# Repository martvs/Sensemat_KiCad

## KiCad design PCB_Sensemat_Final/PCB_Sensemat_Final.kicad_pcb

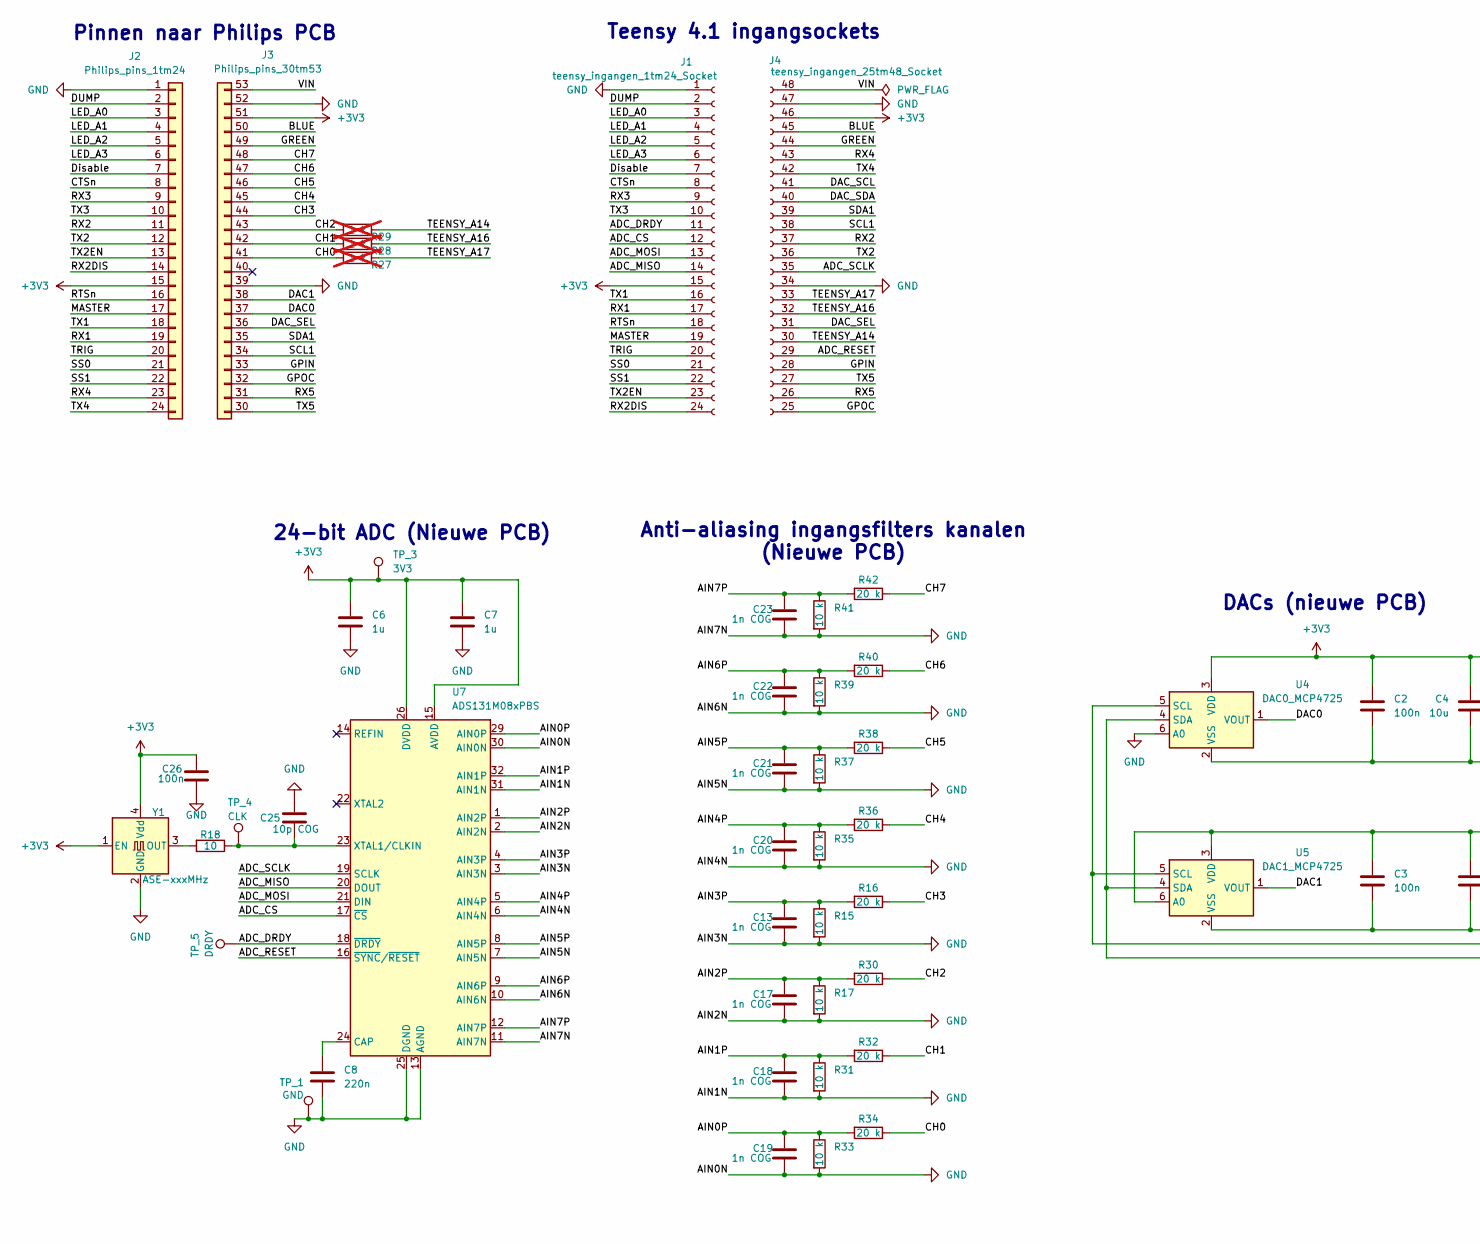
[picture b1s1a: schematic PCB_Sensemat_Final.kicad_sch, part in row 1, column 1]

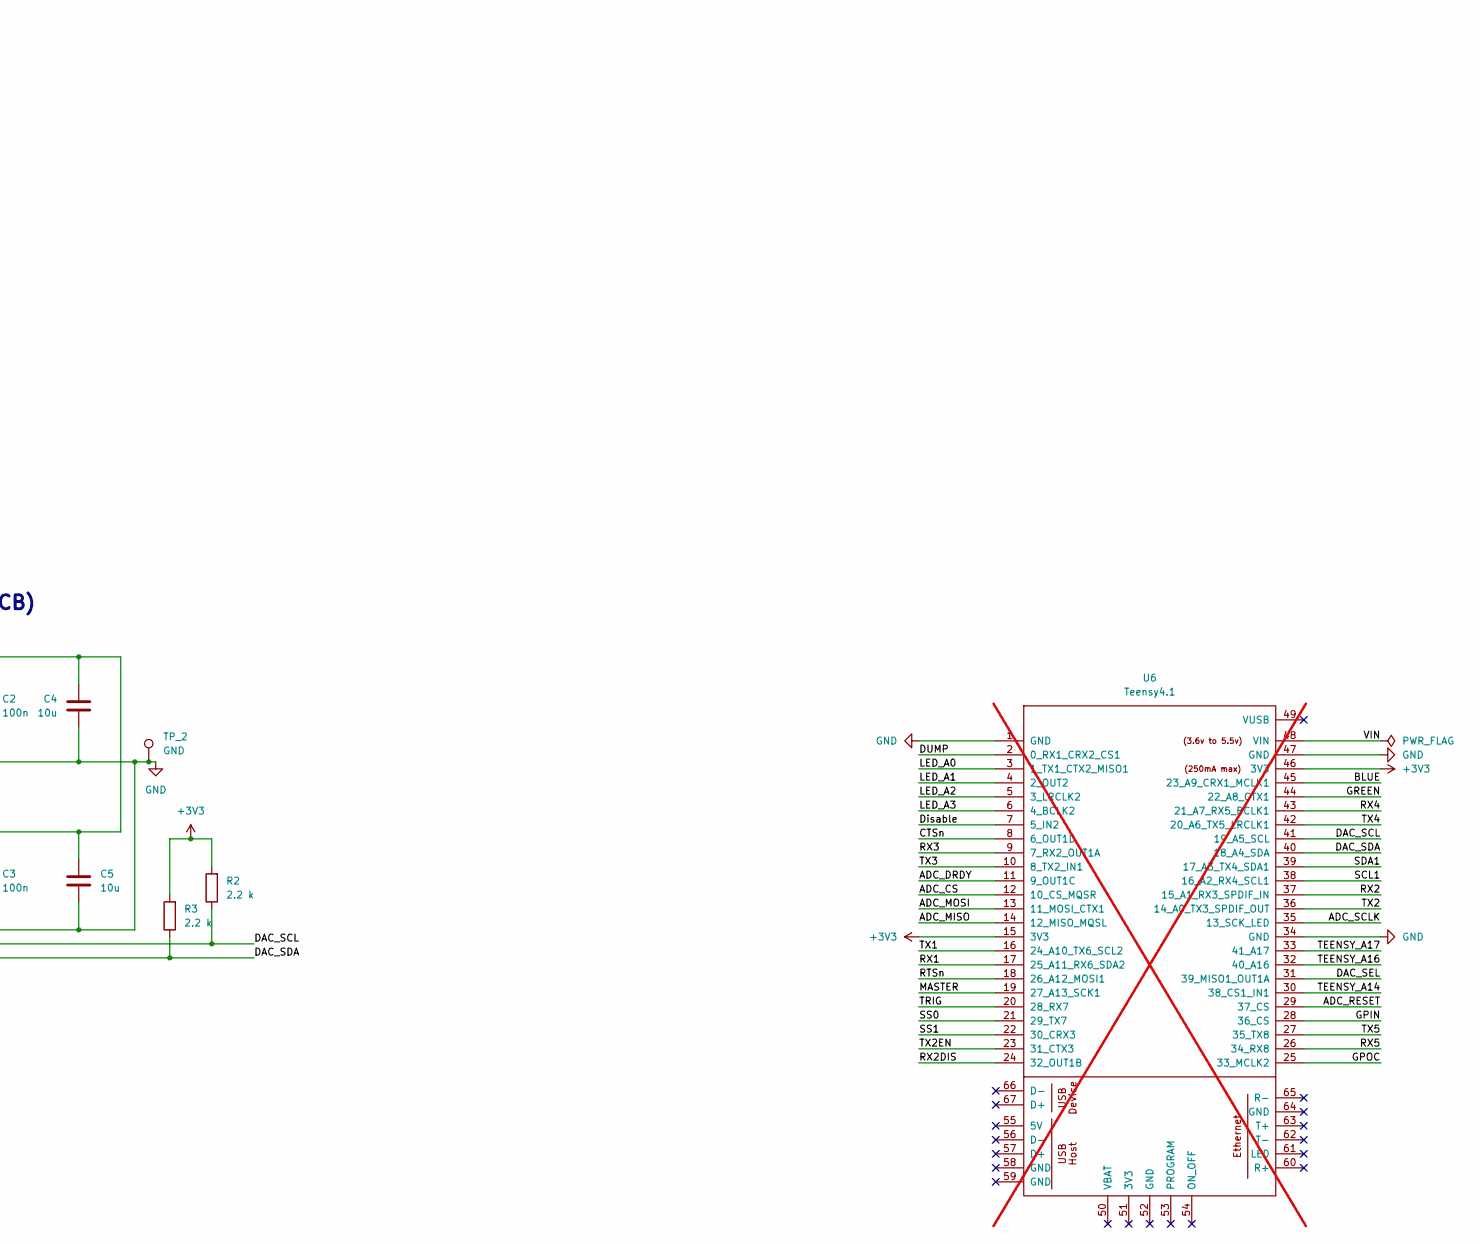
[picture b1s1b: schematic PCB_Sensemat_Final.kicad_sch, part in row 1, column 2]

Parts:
C2, C3, C26: 100n; C_0805_2012Metric_Pad1.18x1.45mm_HandSolder; LCSC C49678
C4, C5: 10u; C_0805_2012Metric_Pad1.18x1.45mm_HandSolder; LCSC C15850
C6, C7: 1u; C_0805_2012Metric_Pad1.18x1.45mm_HandSolder; LCSC C28323
C8: 220n; C_0805_2012Metric_Pad1.18x1.45mm_HandSolder; LCSC C5378
C13, C17, C18, C19, C20, C21, C22, C23: 1n COG; C_0805_2012Metric_Pad1.18x1.45mm_HandSolder; LCSC C29925
C25: 10p COG; C_0805_2012Metric_Pad1.18x1.45mm_HandSolder; LCSC C107107
J1: teensy_ingangen_1tm24_Socket; PinSocket_1x24_P2.54mm_Vertical
J2: Philips_pins_1tm24; PinHeader_1x24_P2.54mm_Vertical
J3: Philips_pins_30tm53; PinHeader_1x24_nieuw_final_P2.54mm_Vertical
J4: teensy_ingangen_25tm48_Socket; PinSocket_ingang_teensy_1x24_P2.54mm_Vertical
R2, R3: 2.2 k; R_0805_2012Metric_Pad1.20x1.40mm_HandSolder; LCSC C17520
R15, R17, R31, R33, R35, R37, R39, R41: 10 k; R_0805_2012Metric_Pad1.20x1.40mm_HandSolder; LCSC C346681
R16, R30, R32, R34, R36, R38, R40, R42: 20 k; R_0805_2012Metric_Pad1.20x1.40mm_HandSolder; LCSC C844680
R18: 10; R_0805_2012Metric_Pad1.20x1.40mm_HandSolder; LCSC C17415
R27, R28, R29: 1 k; R_0805_2012Metric_Pad1.20x1.40mm_HandSolder; not fitted
TP_1, TP_2: GND; TestPoint_THTPad_D2.0mm_Drill1.0mm
TP_3: 3V3; TestPoint_Pad_D1.5mm
TP_4: CLK; TestPoint_Pad_D1.5mm
TP_5: DRDY; TestPoint_Pad_D1.5mm
U4: DAC0_MCP4725; SOT-23-6; LCSC C144198
U5: DAC1_MCP4725; SOT-23-6; LCSC C144198
U6: Teensy4.1; Teensy41; not fitted
U7: ADS131M08xPBS; TQFP-32_5x5mm_P0.5mm; LCSC C2862610
Y1: ASE-xxxMHz; Oscillator_SMD_Abracon_ASE-4Pin_3.2x2.5mm; LCSC C252332

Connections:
+3V3: C2.1, C3.1, C4.1, C5.1, C6.1, C7.1, C26.1, J1.15, J2.15, J3.51 (Pin_3), J4.46 (Pin_3), R2.2, R3.2, TP_3.1 (1_1), U4.3 (VDD), U5.3 (VDD), U5.6 (A0), U6.15 (3V3), U6.46 (3V3), U7.15 (AVDD), U7.26 (DVDD), Y1.1 (EN), Y1.4 (Vdd)
/ADC_CS: J1.12, U6.12 (10_CS_MQSR), U7.17 (~CS)
/ADC_DRDY: J1.11, TP_5.1 (1_1), U6.11 (9_OUT1C), U7.18 (~DRDY)
/ADC_MISO: J1.14, U6.14 (12_MISO_MQSL), U7.20 (DOUT)
/ADC_MOSI: J1.13, U6.13 (11_MOSI_CTX1), U7.21 (DIN)
/ADC_RESET: J4.29 (Pin_20), U6.29 (37_CS), U7.16 (~SYNC/~RESET)
/ADC_SCLK: J4.35 (Pin_14), U6.35 (13_SCK_LED), U7.19 (SCLK)
/AIN0P: C19.1, R33.1, R34.2, U7.29 (AIN0P)
/AIN1P: C18.1, R31.1, R32.2, U7.32 (AIN1P)
/AIN2P: C17.1, R17.1, R30.2, U7.1 (AIN2P)
/AIN3P: C13.1, R15.1, R16.2, U7.4 (AIN3P)
/AIN4P: C20.1, R35.1, R36.2, U7.5 (AIN4P)
/AIN5P: C21.1, R37.1, R38.2, U7.8 (AIN5P)
/AIN6P: C22.1, R39.1, R40.2, U7.9 (AIN6P)
/AIN7P: C23.1, R41.1, R42.2, U7.12 (AIN7P)
/BLUE: J3.50 (Pin_4), J4.45 (Pin_4), U6.45 (23_A9_CRX1_MCLK1)
/CH0: J3.41 (Pin_13), R27.2, R34.1
/CH1: J3.42 (Pin_12), R28.2, R32.1
/CH2: J3.43 (Pin_11), R29.2, R30.1
/CH3: J3.44 (Pin_10), R16.1
/CH4: J3.45 (Pin_9), R36.1
/CH5: J3.46 (Pin_8), R38.1
/CH6: J3.47 (Pin_7), R40.1
/CH7: J3.48 (Pin_6), R42.1
/CTSn: J1.8, J2.8, U6.8 (6_OUT1D)
/DAC0: J3.37 (Pin_17), U4.1 (VOUT)
/DAC1: J3.38 (Pin_16), U5.1 (VOUT)
/DAC_SCL: J4.41 (Pin_8), R2.1, U4.5 (SCL), U5.5 (SCL), U6.41 (19_A5_SCL)
/DAC_SDA: J4.40 (Pin_9), R3.1, U4.4 (SDA), U5.4 (SDA), U6.40 (18_A4_SDA)
/DAC_SEL: J3.36 (Pin_18), J4.31 (Pin_18), U6.31 (39_MISO1_OUT1A)
/DUMP: J1.2, J2.2, U6.2 (0_RX1_CRX2_CS1)
/Disable: J1.7, J2.7, U6.7 (5_IN2)
/GPIN: J3.33 (Pin_21), J4.28 (Pin_21), U6.28 (36_CS)
/GPOC: J3.32 (Pin_22), J4.25 (Pin_24), U6.25 (33_MCLK2)
/GREEN: J3.49 (Pin_5), J4.44 (Pin_5), U6.44 (22_A8_CTX1)
/LED_A0: J1.3, J2.3, U6.3 (1_TX1_CTX2_MISO1)
/LED_A1: J1.4, J2.4, U6.4 (2_OUT2)
/LED_A2: J1.5, J2.5, U6.5 (3_LRCLK2)
/LED_A3: J1.6, J2.6, U6.6 (4_BCLK2)
/MASTER: J1.19, J2.17, U6.19 (27_A13_SCK1)
/RTSn: J1.18, J2.16, U6.18 (26_A12_MOSI1)
/RX1: J1.17, J2.19, U6.17 (25_A11_RX6_SDA2)
/RX2: J2.11, J4.37 (Pin_12), U6.37 (15_A1_RX3_SPDIF_IN)
/RX2DIS: J1.24, J2.14, U6.24 (32_OUT1B)
/RX3: J1.9, J2.9, U6.9 (7_RX2_OUT1A)
/RX4: J2.23, J4.43 (Pin_6), U6.43 (21_A7_RX5_BCLK1)
/RX5: J3.31 (Pin_23), J4.26 (Pin_23), U6.26 (34_RX8)
/SCL1: J3.34 (Pin_20), J4.38 (Pin_11), U6.38 (16_A2_RX4_SCL1)
/SDA1: J3.35 (Pin_19), J4.39 (Pin_10), U6.39 (17_A3_TX4_SDA1)
/SS0: J1.21, J2.21, U6.21 (29_TX7)
/SS1: J1.22, J2.22, U6.22 (30_CRX3)
/TEENSY_A14: J4.30 (Pin_19), R29.1, U6.30 (38_CS1_IN1)
/TEENSY_A16: J4.32 (Pin_17), R28.1, U6.32 (40_A16)
/TEENSY_A17: J4.33, R27.1, U6.33 (41_A17)
/TRIG: J1.20, J2.20, U6.20 (28_RX7)
/TX1: J1.16, J2.18, U6.16 (24_A10_TX6_SCL2)
/TX2: J2.12, J4.36 (Pin_13), U6.36 (14_A0_TX3_SPDIF_OUT)
/TX2EN: J1.23, J2.13, U6.23 (31_CTX3)
/TX3: J1.10, J2.10, U6.10 (8_TX2_IN1)
/TX4: J2.24, J4.42 (Pin_7), U6.42 (20_A6_TX5_LRCLK1)
/TX5: J3.30 (Pin_24), J4.27 (Pin_22), U6.27 (35_TX8)
/VIN: J3.53 (Pin_1), J4.48 (Pin_1), U6.48 (VIN)
GND: C2.2, C3.2, C4.2, C5.2, C6.2, C7.2, C8.2, C13.2, C17.2, C18.2, C19.2, C20.2, C21.2, C22.2, C23.2, C25.1, C26.2, J1.1, J2.1, J3.39 (Pin_15), J3.52 (Pin_2), J4.34 (Pin_15), J4.47 (Pin_2), R15.2, R17.2, R31.2, R33.2, R35.2, R37.2, R39.2, R41.2, TP_1.1 (1_1), TP_2.1 (1_1), U4.2 (VSS), U4.6 (A0), U5.2 (VSS), U6.1 (GND), U6.34 (GND), U6.47 (GND), U7.2 (AIN2N), U7.3 (AIN3N), U7.6 (AIN4N), U7.7 (AIN5N), U7.10 (AIN6N), U7.11 (AIN7N), U7.13 (AGND), U7.25 (DGND), U7.27 (AGND), U7.28 (AGND), U7.30 (AIN0N), U7.31 (AIN1N), Y1.2 (GND)
unnamed: C8.1, U7.24 (CAP)
unnamed: C25.2, R18.1, TP_4.1 (1_1), U7.23 (XTAL1/CLKIN)
unnamed: R18.2, Y1.3 (OUT)

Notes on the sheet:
Teensy 4.1 ingangsockets
DACs (nieuwe PCB)
24-bit ADC (Nieuwe PCB)
Pinnen naar Philips PCB
Anti-aliasing ingangsfilters kanalen (Nieuwe PCB)

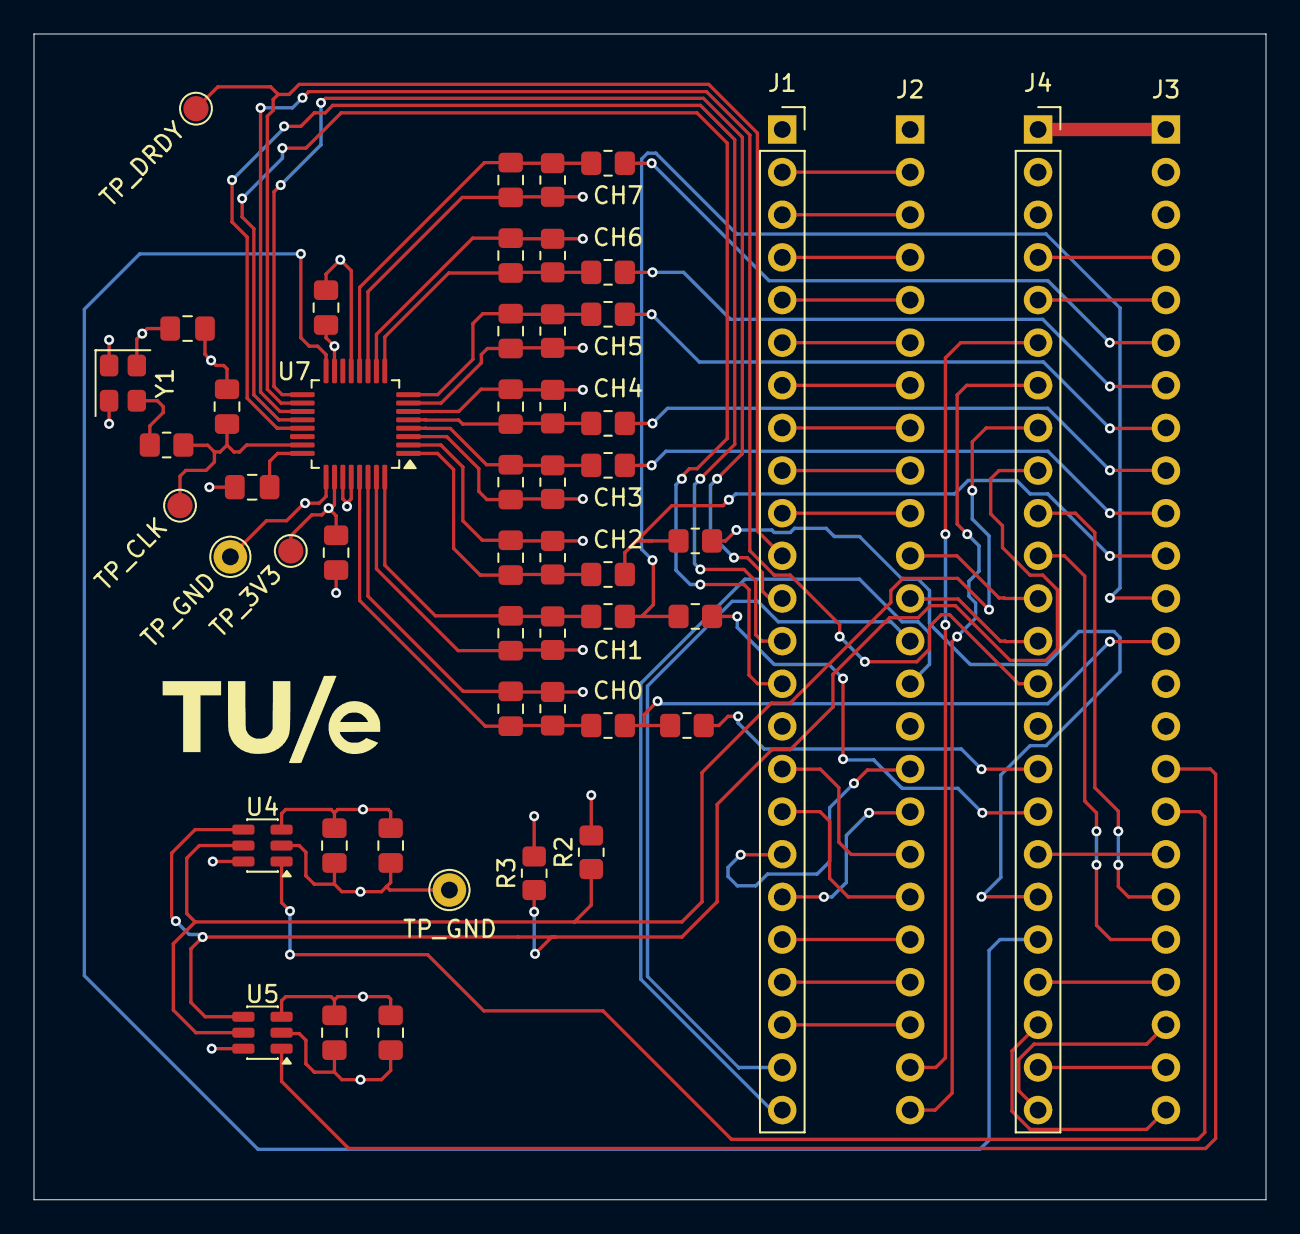
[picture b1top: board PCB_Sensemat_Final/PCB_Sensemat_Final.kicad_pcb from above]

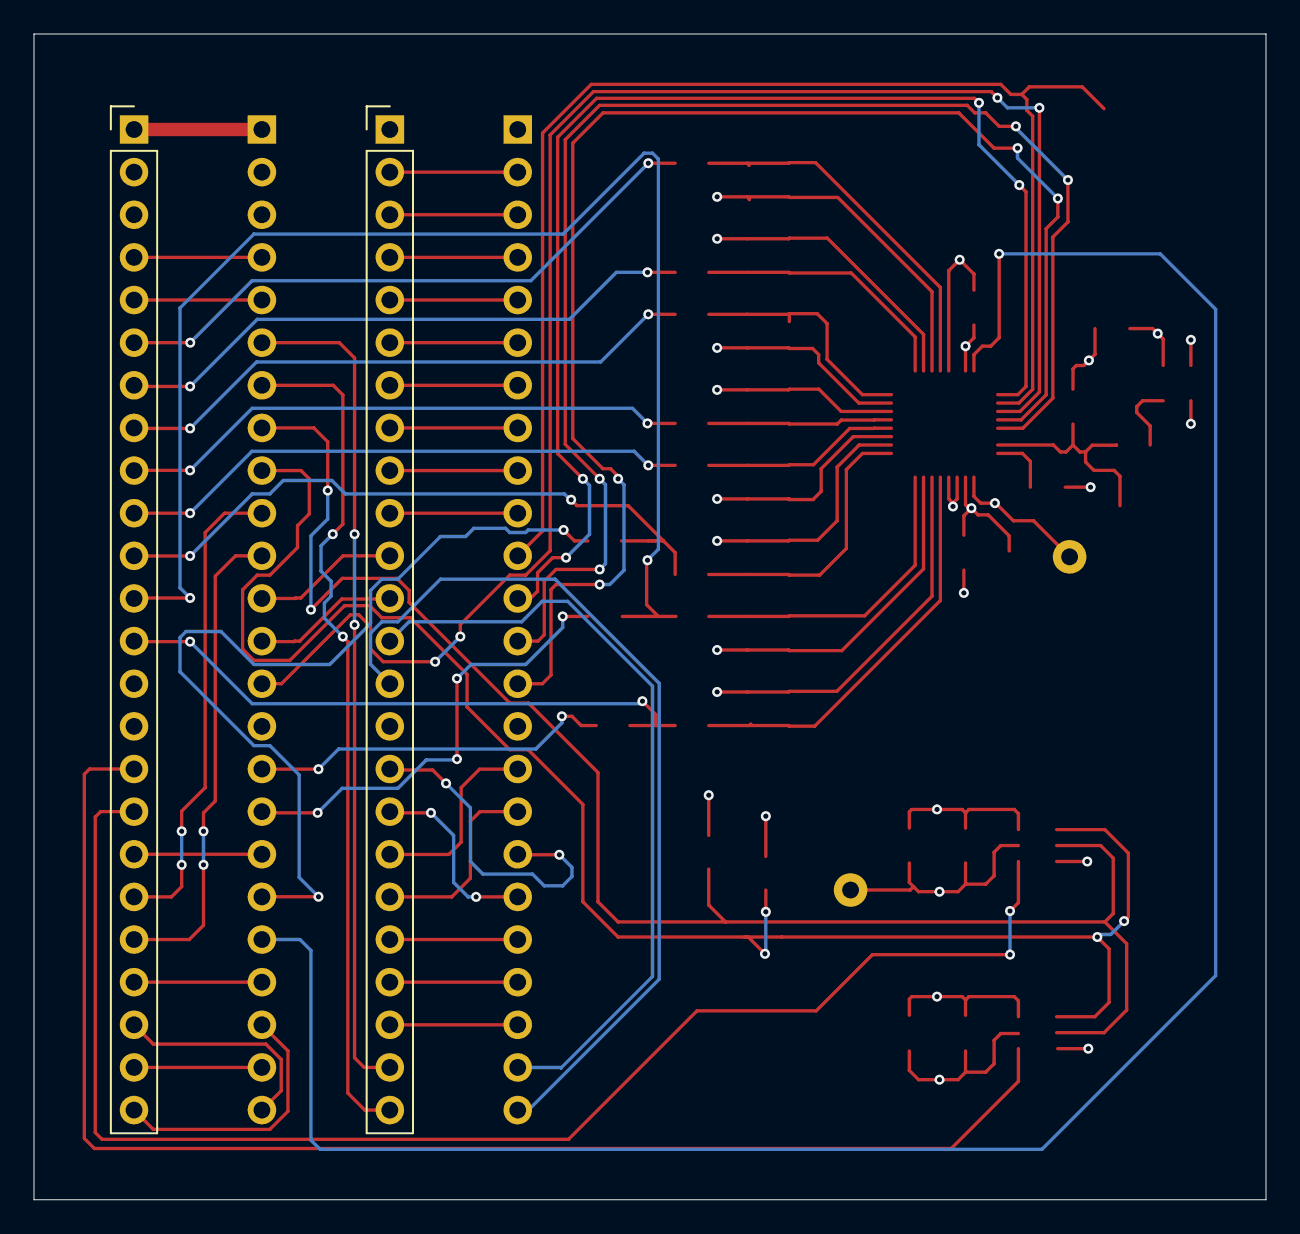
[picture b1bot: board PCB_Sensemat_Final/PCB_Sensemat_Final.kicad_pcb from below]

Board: 4 copper layers, 73.4 x 69.5 mm, 52 parts (2 on the bottom side), 66 nets.

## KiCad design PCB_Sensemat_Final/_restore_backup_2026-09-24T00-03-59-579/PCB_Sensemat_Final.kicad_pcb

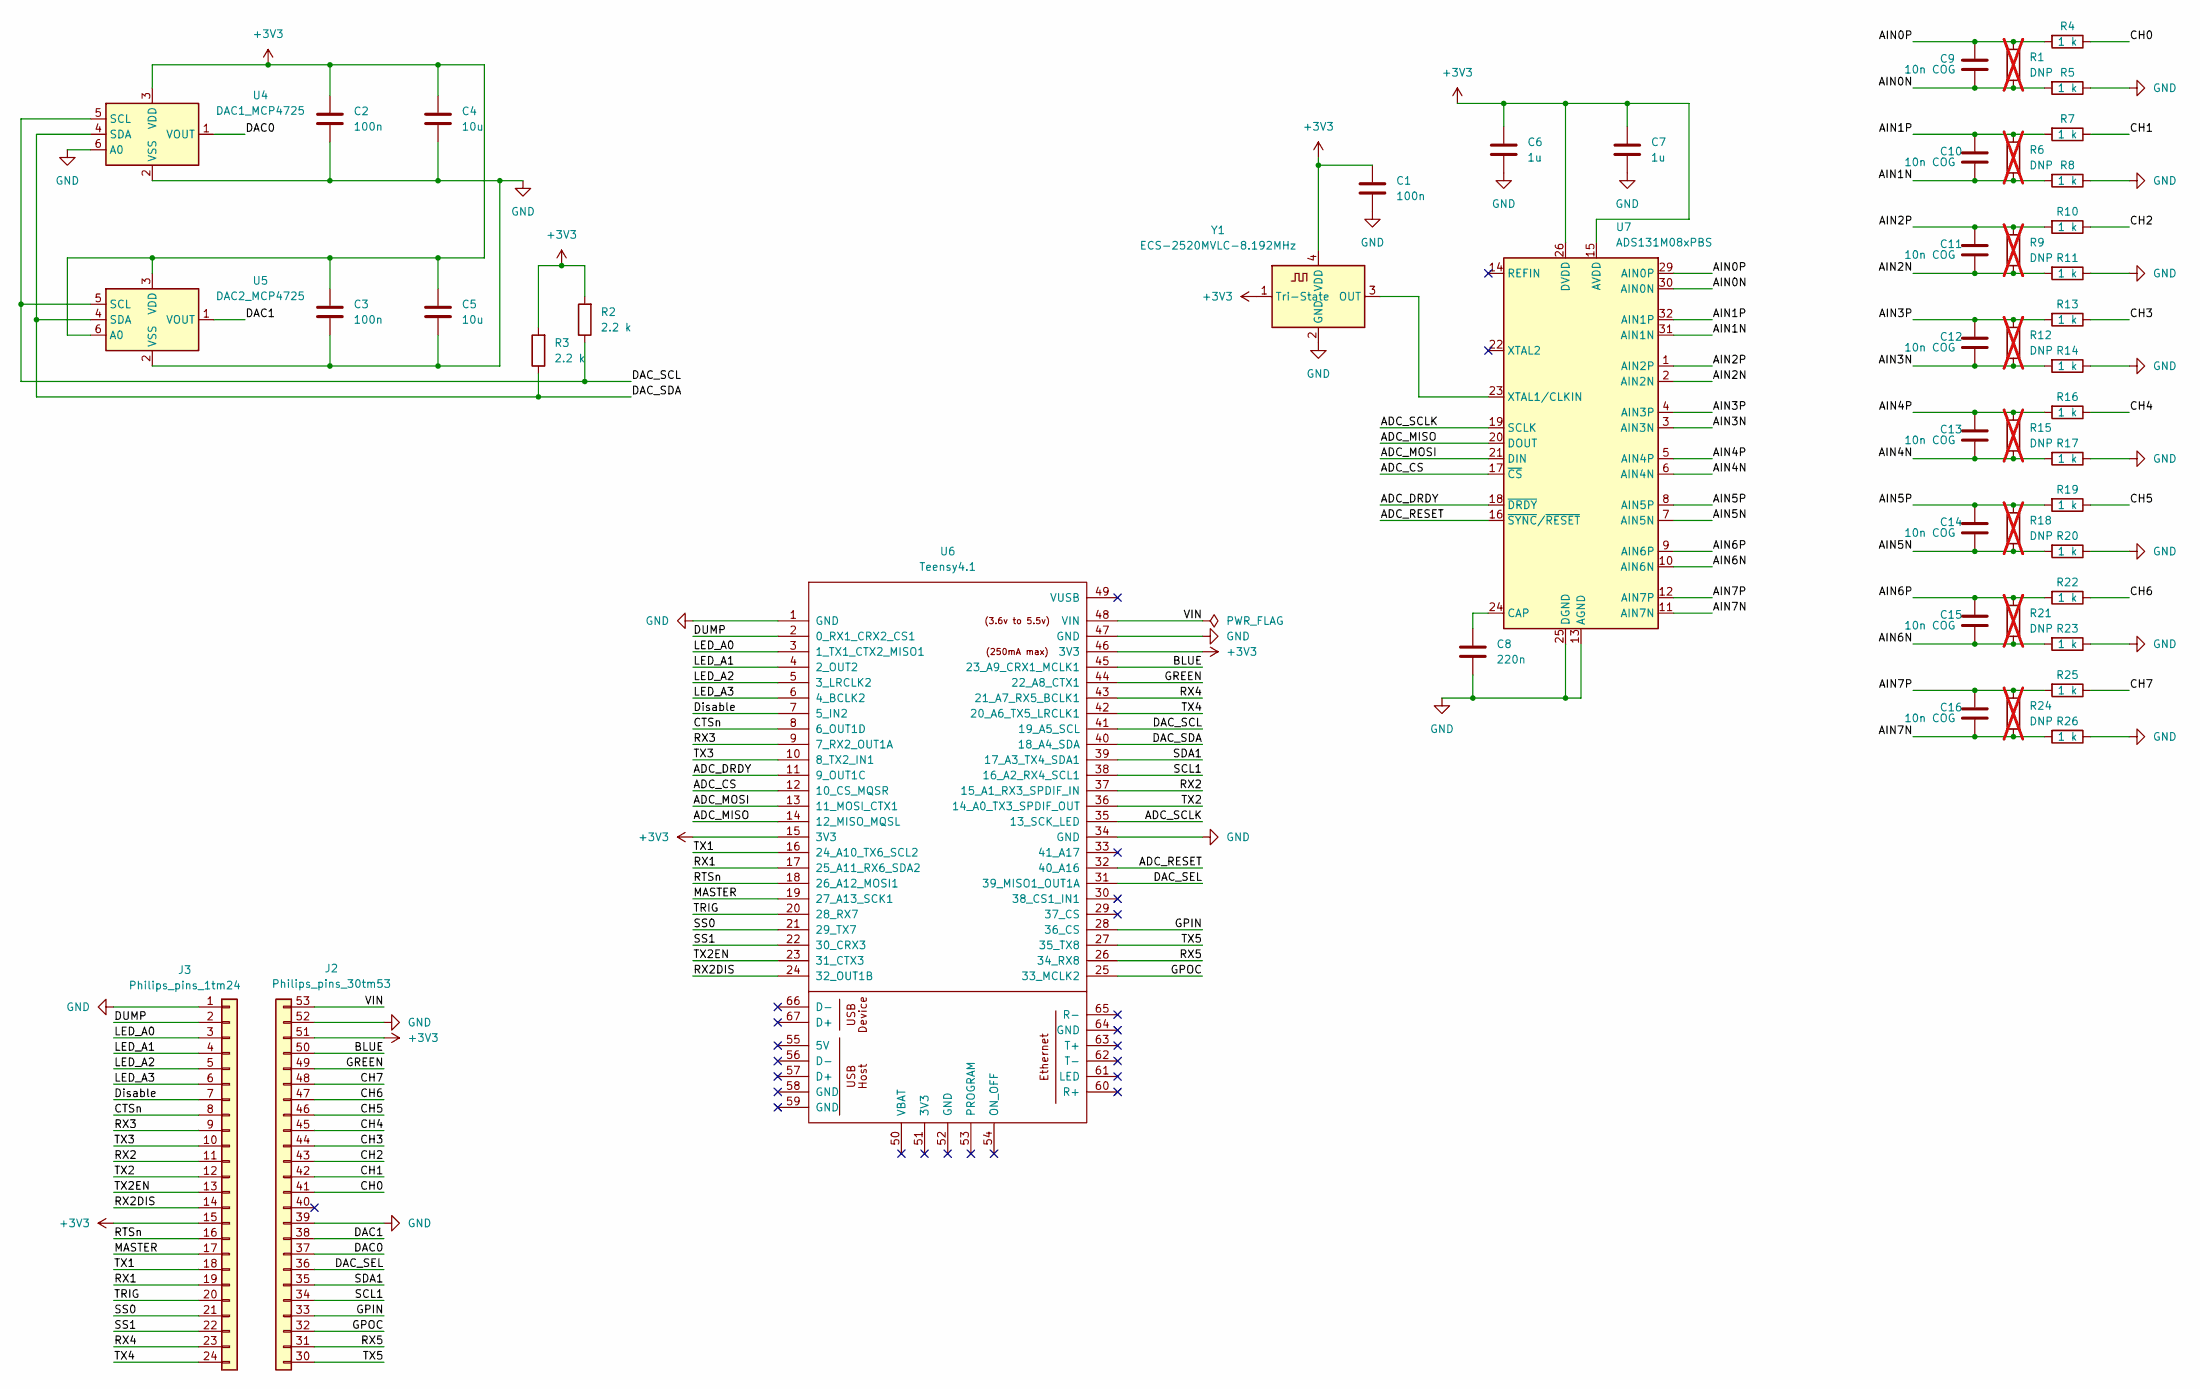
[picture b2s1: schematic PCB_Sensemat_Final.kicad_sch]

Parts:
C1, C2, C3: 100n; C_0805_2012Metric_Pad1.18x1.45mm_HandSolder
C4, C5: 10u; C_0805_2012Metric_Pad1.18x1.45mm_HandSolder
C6, C7: 1u; C_0805_2012Metric_Pad1.18x1.45mm_HandSolder
C8: 220n; C_0805_2012Metric_Pad1.18x1.45mm_HandSolder
C9, C10, C11, C12, C13, C14, C15, C16: 10n COG; C_0805_2012Metric_Pad1.18x1.45mm_HandSolder
J2: Philips_pins_30tm53; PinHeader_1x24_P2.54mm_Vertical_Pins30-53
J3: Philips_pins_1tm24; PinHeader_1x24_P2.54mm_Vertical
R1, R6, R9, R12, R15, R18, R21, R24: DNP; R_0805_2012Metric_Pad1.20x1.40mm_HandSolder; not fitted
R2, R3: 2.2 k; R_0805_2012Metric_Pad1.20x1.40mm_HandSolder
R4, R5, R7, R8, R10, R11, R13, R14, R16, R17, R19, R20, R22, R23, R25, R26: 1 k; R_0805_2012Metric_Pad1.20x1.40mm_HandSolder
U4: DAC1_MCP4725; SOT-23-6
U5: DAC2_MCP4725; SOT-23-6
U6: Teensy4.1; Teensy41
U7: ADS131M08xPBS; TQFP-32_5x5mm_P0.5mm
Y1: ECS-2520MVLC-8.192MHz; Oscillator_SMD_ECS_2520MV-xxx-xx-4Pin_2.5x2.0mm; Mouser-nummer 520-2520MVL08192BNTR

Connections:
+3V3: C1.1, C2.1, C3.1, C4.1, C5.1, C6.1, C7.1, J2.51 (Pin_3), J3.15, R2.2, R3.2, U4.3 (VDD), U5.3 (VDD), U5.6 (A0), U6.15 (3V3), U6.46 (3V3), U7.15 (AVDD), U7.26 (DVDD), Y1.1 (Tri-State), Y1.4 (VDD)
/ADC_CS: U6.12 (10_CS_MQSR), U7.17 (~CS)
/ADC_DRDY: U6.11 (9_OUT1C), U7.18 (~DRDY)
/ADC_MISO: U6.14 (12_MISO_MQSL), U7.20 (DOUT)
/ADC_MOSI: U6.13 (11_MOSI_CTX1), U7.21 (DIN)
/ADC_RESET: U6.32 (40_A16), U7.16 (~SYNC/~RESET)
/ADC_SCLK: U6.35 (13_SCK_LED), U7.19 (SCLK)
/AIN0N: C9.2, R1.2, R5.2, U7.30 (AIN0N)
/AIN0P: C9.1, R1.1, R4.2, U7.29 (AIN0P)
/AIN1N: C10.2, R6.2, R8.2, U7.31 (AIN1N)
/AIN1P: C10.1, R6.1, R7.2, U7.32 (AIN1P)
/AIN2N: C11.2, R9.2, R11.2, U7.2 (AIN2N)
/AIN2P: C11.1, R9.1, R10.2, U7.1 (AIN2P)
/AIN3N: C12.2, R12.2, R14.2, U7.3 (AIN3N)
/AIN3P: C12.1, R12.1, R13.2, U7.4 (AIN3P)
/AIN4N: C13.2, R15.2, R17.2, U7.6 (AIN4N)
/AIN4P: C13.1, R15.1, R16.2, U7.5 (AIN4P)
/AIN5N: C14.2, R18.2, R20.2, U7.7 (AIN5N)
/AIN5P: C14.1, R18.1, R19.2, U7.8 (AIN5P)
/AIN6N: C15.2, R21.2, R23.2, U7.10 (AIN6N)
/AIN6P: C15.1, R21.1, R22.2, U7.9 (AIN6P)
/AIN7N: C16.2, R24.2, R26.2, U7.11 (AIN7N)
/AIN7P: C16.1, R24.1, R25.2, U7.12 (AIN7P)
/BLUE: J2.50 (Pin_4), U6.45 (23_A9_CRX1_MCLK1)
/CH0: J2.41 (Pin_13), R4.1
/CH1: J2.42 (Pin_12), R7.1
/CH2: J2.43 (Pin_11), R10.1
/CH3: J2.44 (Pin_10), R13.1
/CH4: J2.45 (Pin_9), R16.1
/CH5: J2.46 (Pin_8), R19.1
/CH6: J2.47 (Pin_7), R22.1
/CH7: J2.48 (Pin_6), R25.1
/CTSn: J3.8, U6.8 (6_OUT1D)
/DAC0: J2.37 (Pin_17), U4.1 (VOUT)
/DAC1: J2.38 (Pin_16), U5.1 (VOUT)
/DAC_SCL: R2.1, U4.5 (SCL), U5.5 (SCL), U6.41 (19_A5_SCL)
/DAC_SDA: R3.1, U4.4 (SDA), U5.4 (SDA), U6.40 (18_A4_SDA)
/DAC_SEL: J2.36 (Pin_18), U6.31 (39_MISO1_OUT1A)
/DUMP: J3.2, U6.2 (0_RX1_CRX2_CS1)
/Disable: J3.7, U6.7 (5_IN2)
/GPIN: J2.33 (Pin_21), U6.28 (36_CS)
/GPOC: J2.32 (Pin_22), U6.25 (33_MCLK2)
/GREEN: J2.49 (Pin_5), U6.44 (22_A8_CTX1)
/LED_A0: J3.3, U6.3 (1_TX1_CTX2_MISO1)
/LED_A1: J3.4, U6.4 (2_OUT2)
/LED_A2: J3.5, U6.5 (3_LRCLK2)
/LED_A3: J3.6, U6.6 (4_BCLK2)
/MASTER: J3.17, U6.19 (27_A13_SCK1)
/RTSn: J3.16, U6.18 (26_A12_MOSI1)
/RX1: J3.19, U6.17 (25_A11_RX6_SDA2)
/RX2: J3.11, U6.37 (15_A1_RX3_SPDIF_IN)
/RX2DIS: J3.14, U6.24 (32_OUT1B)
/RX3: J3.9, U6.9 (7_RX2_OUT1A)
/RX4: J3.23, U6.43 (21_A7_RX5_BCLK1)
/RX5: J2.31 (Pin_23), U6.26 (34_RX8)
/SCL1: J2.34 (Pin_20), U6.38 (16_A2_RX4_SCL1)
/SDA1: J2.35 (Pin_19), U6.39 (17_A3_TX4_SDA1)
/SS0: J3.21, U6.21 (29_TX7)
/SS1: J3.22, U6.22 (30_CRX3)
/TRIG: J3.20, U6.20 (28_RX7)
/TX1: J3.18, U6.16 (24_A10_TX6_SCL2)
/TX2: J3.12, U6.36 (14_A0_TX3_SPDIF_OUT)
/TX2EN: J3.13, U6.23 (31_CTX3)
/TX3: J3.10, U6.10 (8_TX2_IN1)
/TX4: J3.24, U6.42 (20_A6_TX5_LRCLK1)
/TX5: J2.30 (Pin_24), U6.27 (35_TX8)
/VIN: J2.53 (Pin_1), U6.48 (VIN)
GND: C1.2, C2.2, C3.2, C4.2, C5.2, C6.2, C7.2, C8.2, J2.39 (Pin_15), J2.52 (Pin_2), J3.1, R5.1, R8.1, R11.1, R14.1, R17.1, R20.1, R23.1, R26.1, U4.2 (VSS), U4.6 (A0), U5.2 (VSS), U6.1 (GND), U6.34 (GND), U6.47 (GND), U7.13 (AGND), U7.25 (DGND), U7.27 (AGND), U7.28 (AGND), Y1.2 (GND)
unnamed: C8.1, U7.24 (CAP)
unnamed: U7.23 (XTAL1/CLKIN), Y1.3 (OUT)

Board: 2 copper layers, 49 parts (2 on the bottom side), 70 nets, no tracks yet.
